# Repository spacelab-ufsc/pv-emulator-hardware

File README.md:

<h1 align="center">
	PV Emulator Hardware
	<br>
</h1>

<h4 align="center">Solar panel emulator based on the single-diode model, designed and developed by SpaceLab.</h4>

<p align="center">

</p>

<p align="center">
  	<a href="#overview">Overview</a> •
  	<a href="#repository-organization">Repository Organization</a> •
  	<a href="#license">License</a> •
  	<a href="#releases">Releases</a> •
  	<a href="#notes">Notes</a>
</p>

## Overview

The **PV Emulator Hardware** project aims to implement a solar panels simulator. The behavior of a solar panel based on the **single-diode model**. This emulator is designed for use in laboratory environments and embedded systems testing, such as MPPT algorithms.

## Repository Organization

- `doc`: Technical documentation.
- `hardware`: Hardware design files and outputs.
- `simulation`: LTspice model used for validating the solar panels behavior.

## License

This project is open-source and distributed under the MIT License. See [LICENSE](./LICENSE) for more information.

## Releases

Releases will be tagged periodically as development progresses. Check the [Releases page](https://github.com/spacelab-ufsc/pv-emulator-hardware/releases) for more details.

## Notes

More information about SpaceLab: [GitHub](https://github.com/spacelab-ufsc/spacelab) • [Website](https://spacelab.ufsc.br/en/home/)

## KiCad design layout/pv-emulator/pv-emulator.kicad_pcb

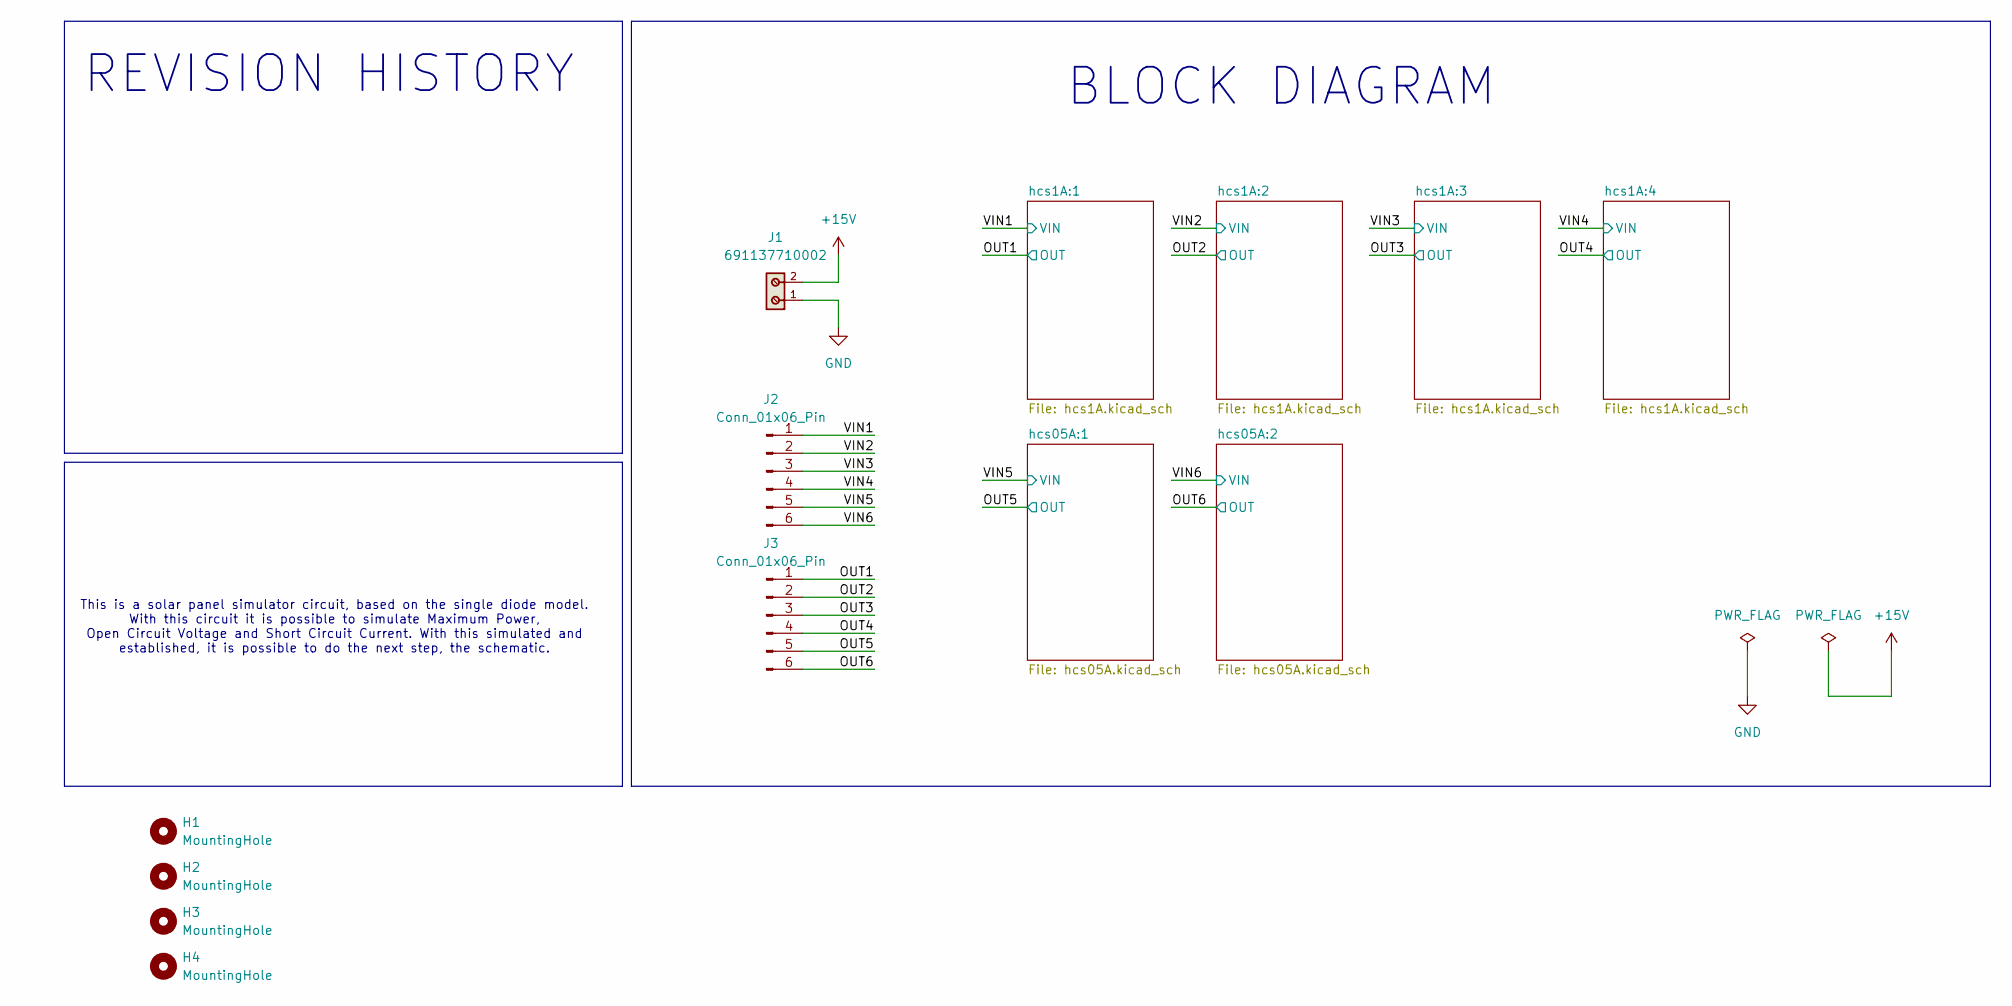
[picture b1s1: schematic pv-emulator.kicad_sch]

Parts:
H1, H2, H3, H4: MountingHole; MountingHole_2.2mm_M2
J1: 691137710002; Manufacturer Part Number 691137710002
J2, J3: Conn_01x06_Pin; PinHeader_1x06_P2.54mm_Vertical

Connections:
+15V: J1.2; also elsewhere on the board
/OUT1: J3.1; also elsewhere on the board
/OUT2: J3.2; also elsewhere on the board
/OUT3: J3.3; also elsewhere on the board
/OUT4: J3.4; also elsewhere on the board
/OUT5: J3.5; also elsewhere on the board
/OUT6: J3.6; also elsewhere on the board
/VIN1: J2.1; also elsewhere on the board
/VIN2: J2.2; also elsewhere on the board
/VIN3: J2.3; also elsewhere on the board
/VIN4: J2.4; also elsewhere on the board
/VIN5: J2.5; also elsewhere on the board
/VIN6: J2.6; also elsewhere on the board
GND: J1.1; also elsewhere on the board

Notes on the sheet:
BLOCK DIAGRAM
This is a solar panel simulator circuit, based on the single diode model. With this circuit it is possible to simulate Maximum Power, Open Circuit Voltage and Short Circuit Current. With this simulated and established, it is possible to do the next step, the schematic.
REVISION HISTORY

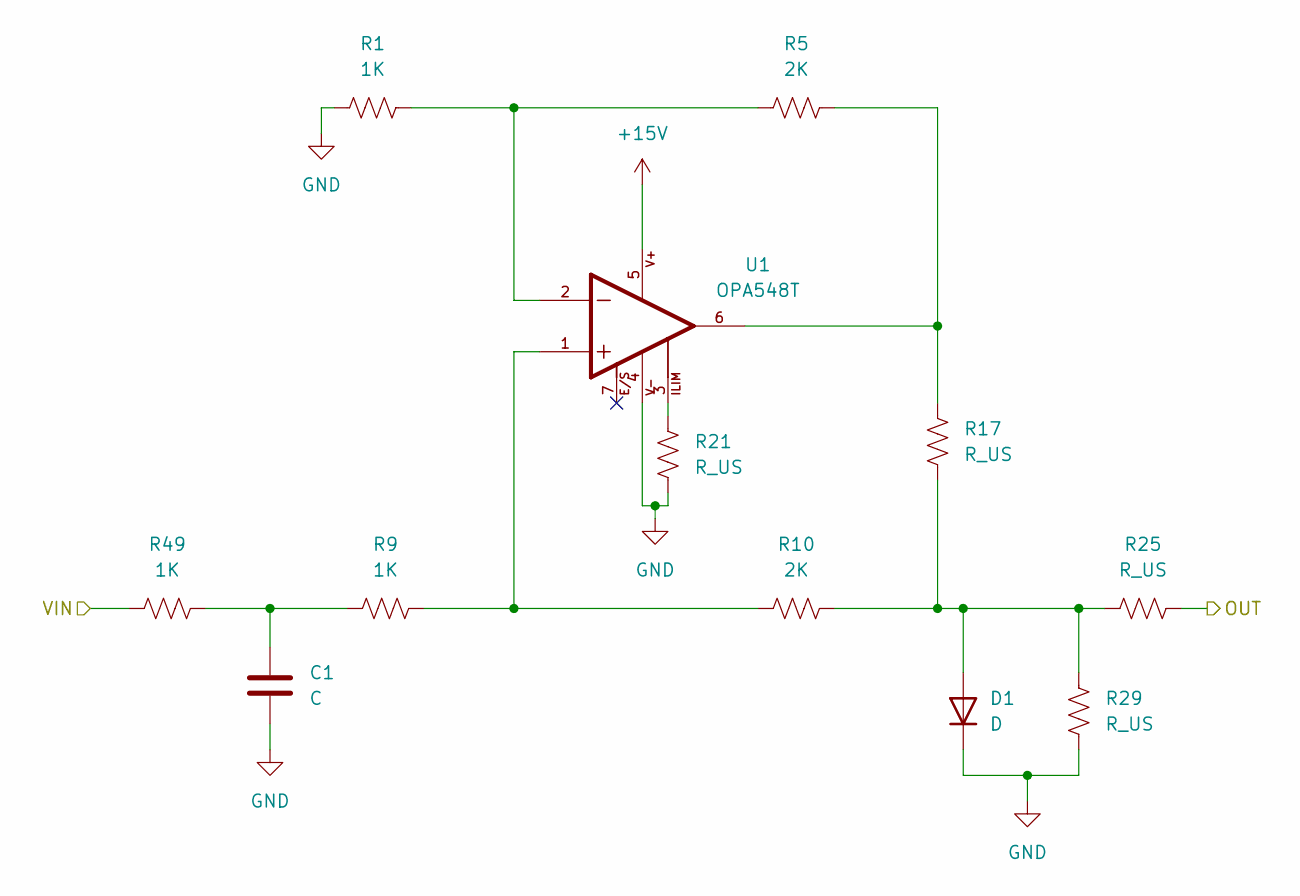
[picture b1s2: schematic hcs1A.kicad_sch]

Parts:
C1: C; C_0603_1608Metric
D1: D; D_0603_1608Metric
R1, R9, R49: 1K; R_0603_1608Metric
R5, R10: 2K; R_0603_1608Metric
R17, R25, R29: R_US; R_Axial_Power_L38.0mm_W9.0mm_P40.64mm
R21: R_US; R_0603_1608Metric
U1: OPA548T; TO127P1016X449X2137-7; Manufacturer Part Number OPA548T

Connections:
+15V: U1.5; also elsewhere on the board
/OUT1: R25.1; also elsewhere on the board
GND: C1.2, D1.1 (K), R1.2, R21.1, R29.1, U1.4; also elsewhere on the board
unnamed 14: C1.1, R9.2; also elsewhere on the board
unnamed: D1.2 (A), R10.1, R17.1, R25.2, R29.2
unnamed: R1.1, R5.2, U1.2
unnamed: R9.1, R10.2, U1.1
unnamed: R5.1, R17.2, U1.6
unnamed: R21.2, U1.3

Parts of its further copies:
C2, C3, C4: C; C_0603_1608Metric
D2, D3, D4: D; D_0603_1608Metric
R2, R3, R4, R11, R13, R15: 1K; R_0603_1608Metric
R6, R7, R8, R12, R14, R16: 2K; R_0603_1608Metric
R18, R19, R20, R26, R27, R28, R30, R31, R32: R_US; R_Axial_Power_L38.0mm_W9.0mm_P40.64mm
R22, R23, R24: R_US; R_0603_1608Metric
U2, U3, U4: OPA548T; TO127P1016X449X2137-7; Manufacturer Part Number OPA548T

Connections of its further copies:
+15V: U2.5, U3.5, U4.5; also elsewhere on the board
/OUT2: R26.1; also elsewhere on the board
/OUT3: R27.1; also elsewhere on the board
/OUT4: R28.1; also elsewhere on the board
GND: C2.2, C3.2, C4.2, D2.1 (K), D3.1 (K), D4.1 (K), R2.2, R3.2, R4.2, R22.1, R23.1, R24.1, R30.1, R31.1, R32.1, U2.4, U3.4, U4.4; also elsewhere on the board
unnamed 15: C2.1, R11.2; also elsewhere on the board
unnamed 16: C3.1, R13.2; also elsewhere on the board
unnamed 17: C4.1, R15.2; also elsewhere on the board
unnamed: D2.2 (A), R12.1, R18.1, R26.2, R30.2
unnamed: D3.2 (A), R14.1, R19.1, R27.2, R31.2
unnamed: D4.2 (A), R16.1, R20.1, R28.2, R32.2
unnamed: R2.1, R6.2, U2.2
unnamed: R3.1, R7.2, U3.2
unnamed: R4.1, R8.2, U4.2
unnamed: R11.1, R12.2, U2.1
unnamed: R13.1, R14.2, U3.1
unnamed: R15.1, R16.2, U4.1
unnamed: R6.1, R18.2, U2.6
unnamed: R7.1, R19.2, U3.6
unnamed: R8.1, R20.2, U4.6
unnamed: R22.2, U2.3
unnamed: R23.2, U3.3
unnamed: R24.2, U4.3

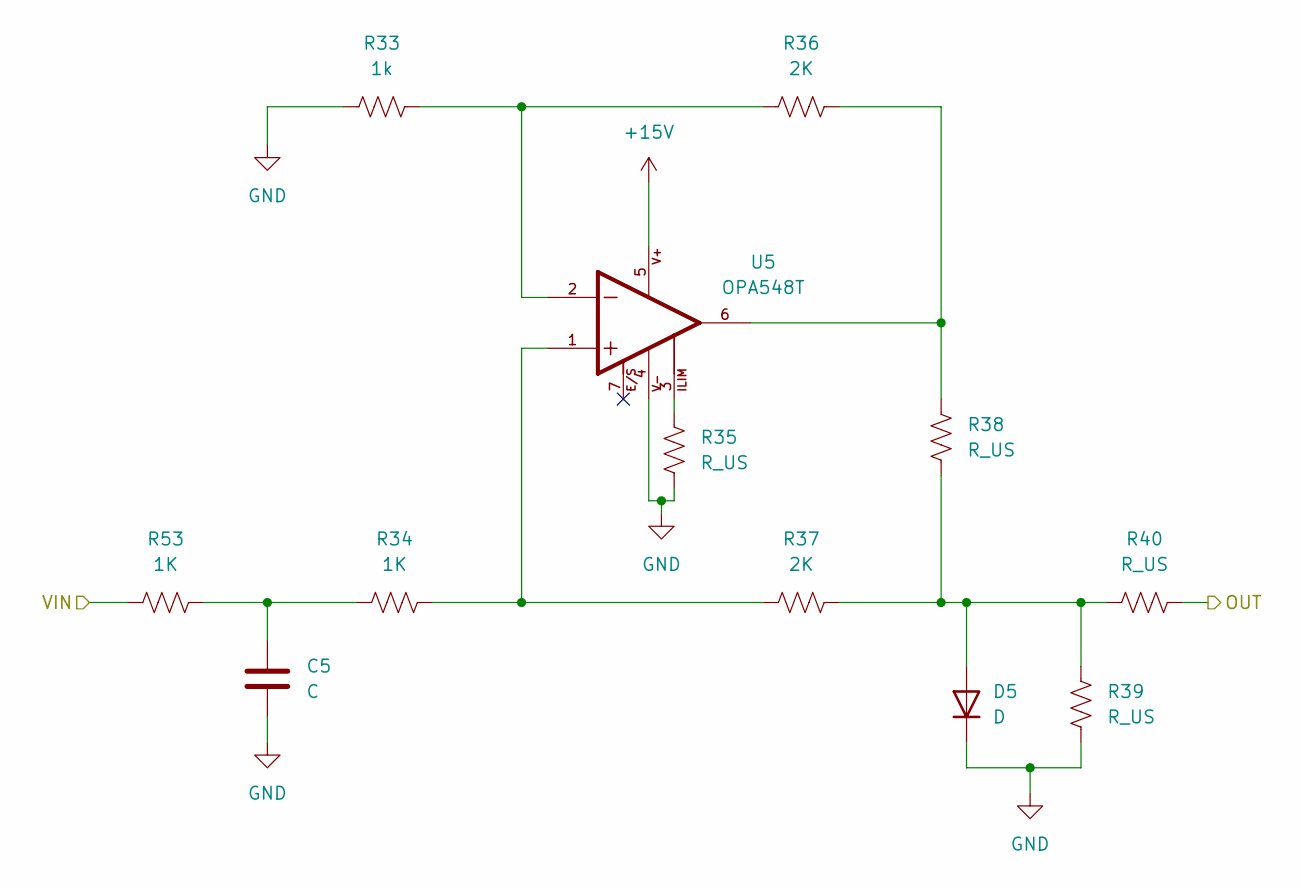
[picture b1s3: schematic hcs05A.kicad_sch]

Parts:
C5: C; C_0603_1608Metric
D5: D; D_0603_1608Metric
R33: 1k; R_0603_1608Metric
R34, R53: 1K; R_0603_1608Metric
R35: R_US; R_0603_1608Metric
R36, R37: 2K; R_0603_1608Metric
R38, R39, R40: R_US; R_Axial_Power_L38.0mm_W9.0mm_P40.64mm
U5: OPA548T; TO127P1016X449X2137-7; Manufacturer Part Number OPA548T

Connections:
+15V: U5.5; also elsewhere on the board
/OUT5: R40.1; also elsewhere on the board
GND: C5.2, D5.1 (K), R33.2, R35.1, R39.1, U5.4; also elsewhere on the board
unnamed 18: C5.1, R34.2; also elsewhere on the board
unnamed: D5.2 (A), R37.1, R38.1, R39.2, R40.2
unnamed: R33.1, R36.2, U5.2
unnamed: R34.1, R37.2, U5.1
unnamed: R35.2, U5.3
unnamed: R36.1, R38.2, U5.6

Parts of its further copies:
C6: C; C_0603_1608Metric
D6: D; D_0603_1608Metric
R41: 1k; R_0603_1608Metric
R42: 1K; R_0603_1608Metric
R43: R_US; R_0603_1608Metric
R44, R45: 2K; R_0603_1608Metric
R46, R47, R48: R_US; R_Axial_Power_L38.0mm_W9.0mm_P40.64mm
U6: OPA548T; TO127P1016X449X2137-7; Manufacturer Part Number OPA548T

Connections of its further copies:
+15V: U6.5; also elsewhere on the board
/OUT6: R48.1; also elsewhere on the board
GND: C6.2, D6.1 (K), R41.2, R43.1, R47.1, U6.4; also elsewhere on the board
unnamed 19: C6.1, R42.2; also elsewhere on the board
unnamed: D6.2 (A), R45.1, R46.1, R47.2, R48.2
unnamed: R41.1, R44.2, U6.2
unnamed: R42.1, R45.2, U6.1
unnamed: R43.2, U6.3
unnamed: R44.1, R46.2, U6.6

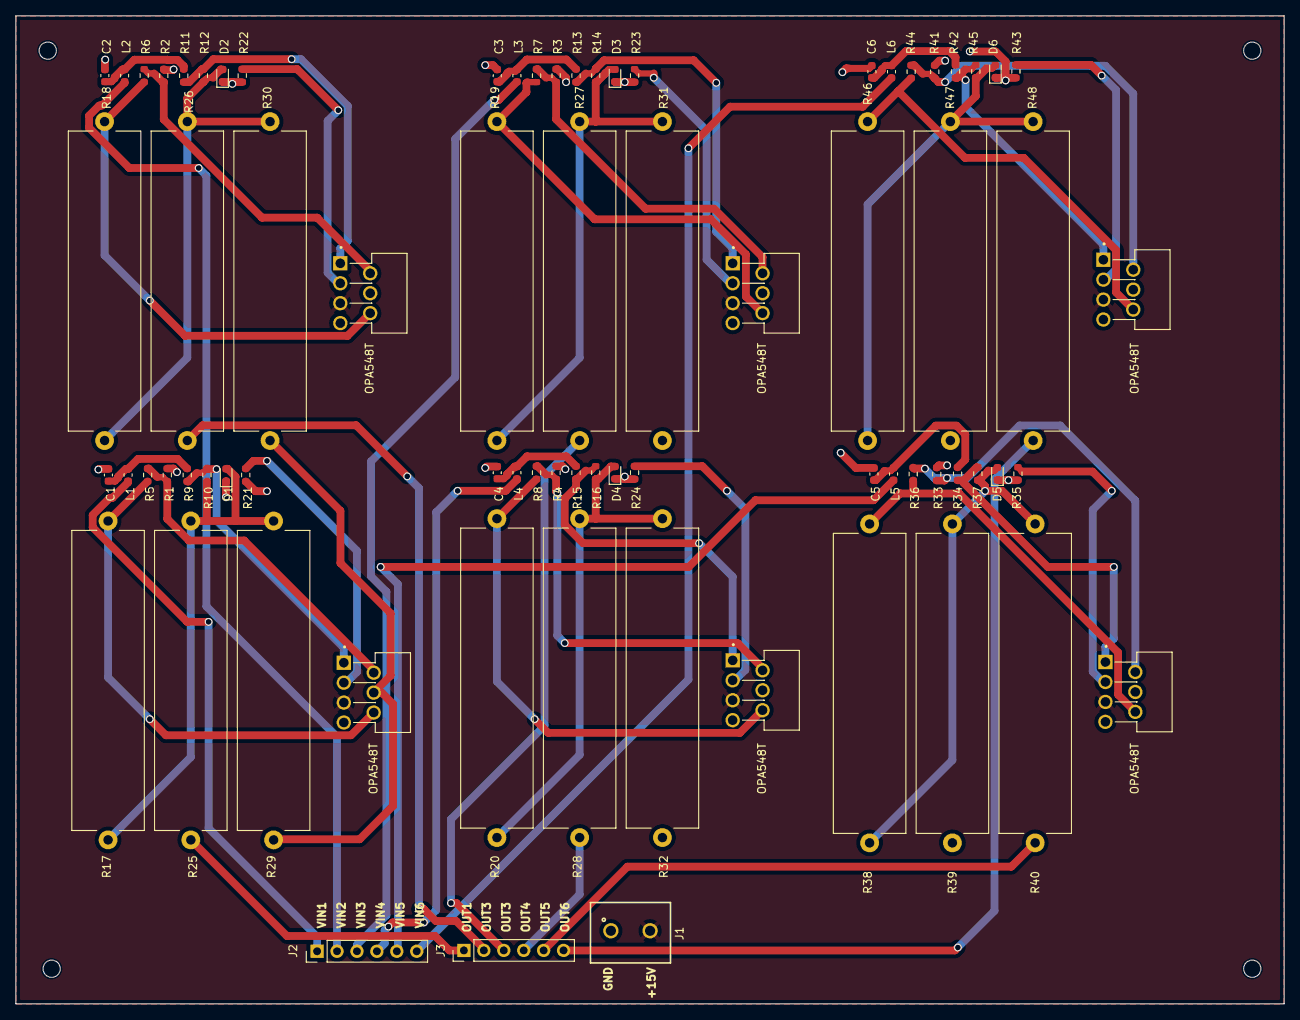
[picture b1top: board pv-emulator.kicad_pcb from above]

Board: 2 copper layers, 161.6 x 125.9 mm, 79 parts (0 on the bottom side), 50 nets.

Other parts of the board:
L1, L2, L3, L4, L5, L6: L; L_0603_1608Metric

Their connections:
/VIN1: L1.1; also elsewhere on the board
/VIN2: L2.1; also elsewhere on the board
/VIN3: L3.1; also elsewhere on the board
/VIN4: L4.1; also elsewhere on the board
/VIN5: L5.1; also elsewhere on the board
/VIN6: L6.1; also elsewhere on the board
unnamed 14: L1.2; also elsewhere on the board
unnamed 15: L2.2; also elsewhere on the board
unnamed 16: L3.2; also elsewhere on the board
unnamed 17: L4.2; also elsewhere on the board
unnamed 18: L5.2; also elsewhere on the board
unnamed 19: L6.2; also elsewhere on the board

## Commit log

2025-08-01 feat(simulations): add solar panel simulation files
2025-08-01 feat(readme): add initial README
2025-08-05 feat(simulations): update solar panel simulation files
2025-08-13 feat(simulations): update solar panel simulation files and added pwm simmulation
2026-01-31 feat: layout
